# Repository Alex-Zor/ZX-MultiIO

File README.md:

Universal Expansion Board for the ZX PentaDiv Nemo
An expansion board for the ZX Spectrum clone that combines multiple I/O devices in one:

💾 Hard disk controller (Nemo IDE) 

📼 Floppy disk controller (BDI)

💡 SD card interface (z-controller)

⏰ Real-time clock (RTC)

The goal of the project is to provide a universal solution for data storage and accurate timekeeping on ZX PentaDiv NEMO computers

https://t.me/pentadiv

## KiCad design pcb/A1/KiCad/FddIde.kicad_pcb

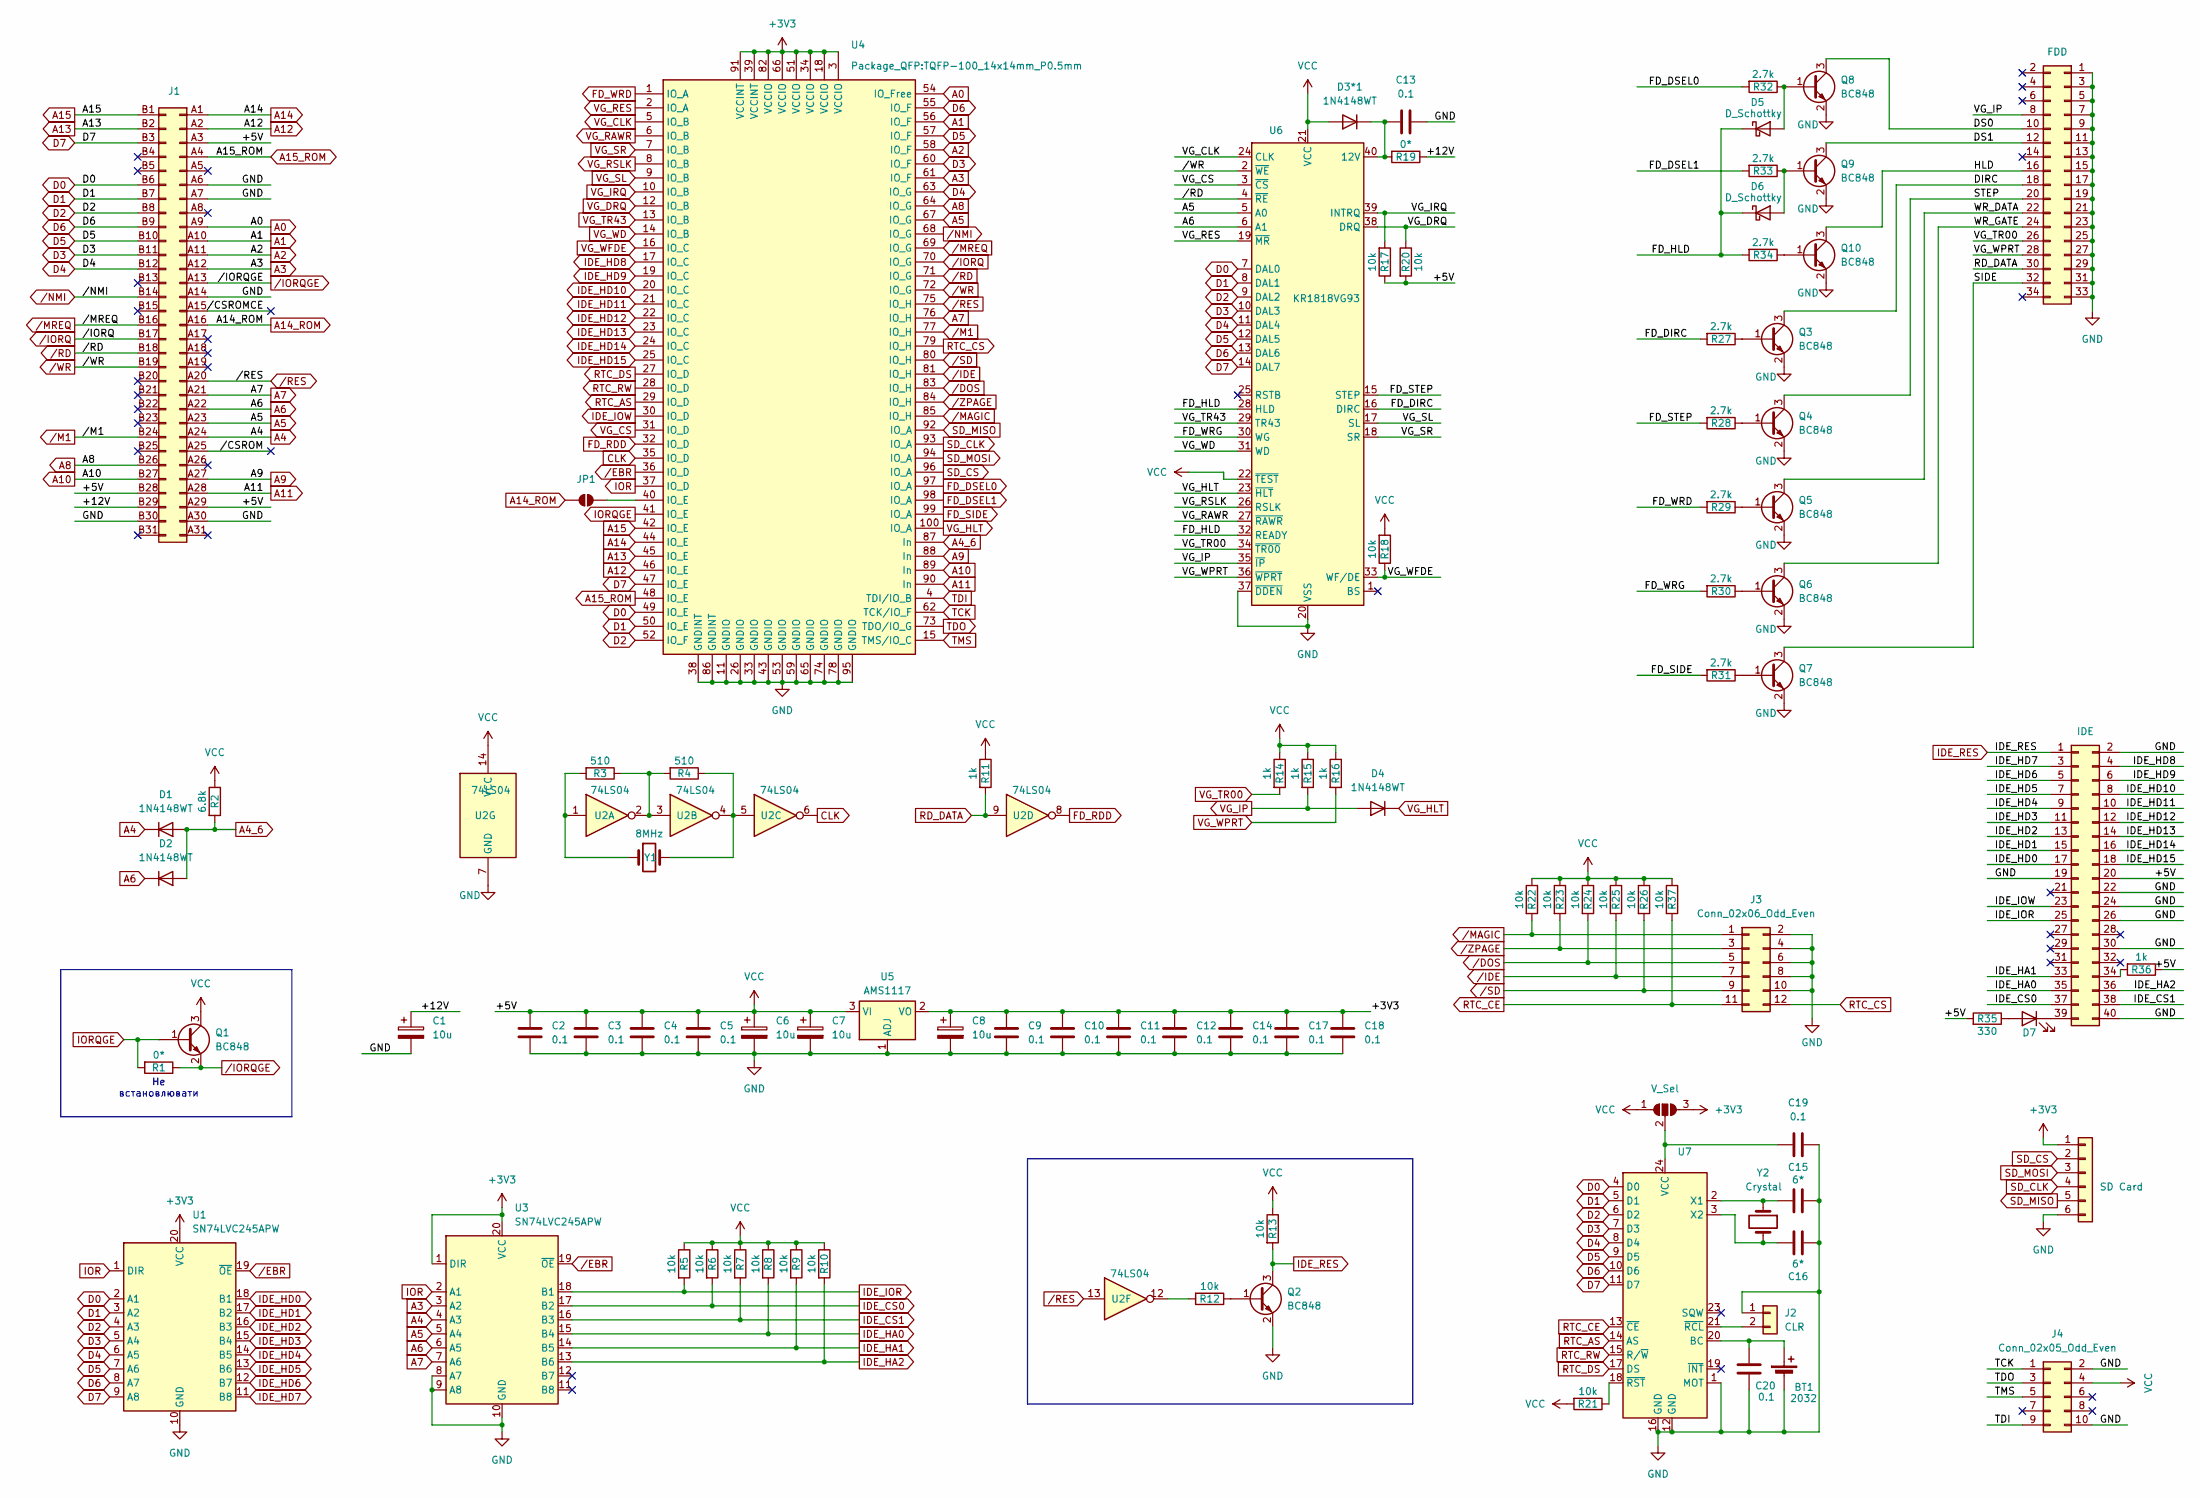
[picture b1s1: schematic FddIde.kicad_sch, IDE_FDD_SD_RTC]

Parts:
BT1: 2032; BatteryHolder_MYOUNG_BS-07-A1BJ001_CR2032
C1, C6, C7, C8: 10u; CP_Radial_D4.0mm_P2.00mm
C2, C3, C4, C5, C9, C10, C11, C12, C13, C14, C17, C18, C19, C20: 0.1; C_0805_2012Metric_Pad1.18x1.45mm_HandSolder
C15, C16: 6*; C_0805_2012Metric_Pad1.18x1.45mm_HandSolder
D1, D2, D3*1, D4: 1N4148WT; D_MiniMELF
D5, D6: D_Schottky; D_MiniMELF
D7: LED; LED_1206_3216Metric_Pad1.42x1.75mm_HandSolder
J1: Conn_02x31_Row_Letter_First; NemoBus_Edge_Connector
J2: CLR; PinHeader_1x02_P2.54mm_Vertical
J3: Conn_02x06_Odd_Even; PinHeader_2x06_P2.54mm_Vertical
J4: Conn_02x05_Odd_Even; PinHeader_2x05_P2.54mm_Vertical
J5: FDD; IDC-Header_2x17_P2.54mm_Vertical
J6: IDE; IDC-Header_2x20_P2.54mm_Vertical
J7: SD Card; PinHeader_1x06_P2.54mm_Vertical
JP1: SolderJumper_2_Open; SolderJumper-2_P1.3mm_Open_RoundedPad1.0x1.5mm
JP2: V_Sel; SolderJumper-3_P1.3mm_Open_RoundedPad1.0x1.5mm
Q1, Q2, Q3, Q4, Q5, Q6, Q7, Q8, Q9, Q10: BC848; SOT-23
R1: 0*; R_0805_2012Metric_Pad1.20x1.40mm_HandSolder
R2: 6.8k; R_0805_2012Metric_Pad1.20x1.40mm_HandSolder
R3, R4: 510; R_0805_2012Metric_Pad1.20x1.40mm_HandSolder
R5, R6, R7, R8, R9, R10, R12, R13, R17, R18, R20, R21, R22, R23, R24, R25, R26, R37: 10k; R_0805_2012Metric_Pad1.20x1.40mm_HandSolder
R11, R14, R15, R16, R36: 1k; R_0805_2012Metric_Pad1.20x1.40mm_HandSolder
R19: 0*; SolderJumper-2_P1.3mm_Open_RoundedPad1.0x1.5mm
R27, R28, R29, R30, R31, R32, R33, R34: 2.7k; R_0805_2012Metric_Pad1.20x1.40mm_HandSolder
R35: 330; R_0805_2012Metric_Pad1.20x1.40mm_HandSolder
U1, U3: SN74LVC245APW; TSSOP-20_4.4x6.5mm_P0.65mm
U2: 74LS04; DIP-14_W7.62mm
U4: TQFP-100_14x14mm_P0.5mm
U5: AMS1117; SOT-223-3_TabPin2
U6: KR1818VG93; DIP-40_W15.24mm
U7: SSOP-24_3.9x8.7mm_P0.635mm
Y1: 8MHz; Crystal_HC49-4H_Vertical
Y2: Crystal; Crystal_DS26_D2.0mm_L6.0mm_Horizontal

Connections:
+3V3: C8.1, C9.1, C10.1, C11.1, C12.1, C14.1, C17.1, C18.1, J7.1, JP2.3 (B), U1.20 (VCC), U3.1 (DIR), U3.20 (VCC), U4.3 (VCCIO), U4.18 (VCCIO), U4.34 (VCCIO), U4.39 (VCCINT), U4.51 (VCCIO), U4.66 (VCCIO), U4.82 (VCCIO), U4.91 (VCCINT), U5.2 (VO)
/+12V: C1.1, J1.B29 (Pin_b29), R19.1
/DIRC: J5.18, Q3.3 (C)
/DS0: J5.10, Q8.3 (C)
/DS1: J5.12, Q9.3 (C)
/FD_DIRC: R27.2, U6.16 (DIRC)
/FD_HLD: D5.1 (K), D6.1 (K), R34.2, U6.28 (HLD), U6.32 (READY)
/FD_STEP: R28.2, U6.15 (STEP)
/FD_WRG: R30.2, U6.30 (WG)
/HLD: J5.16, Q10.3 (C)
/SIDE: J5.32, Q7.3 (C)
/STEP: J5.20, Q4.3 (C)
/WR_DATA: J5.22, Q5.3 (C)
/WR_GATE: J5.24, Q6.3 (C)
//CSROM: J1.A25 (Pin_a25)
//CSROMCE: J1.A15 (Pin_a15)
A0: J1.A9 (Pin_a9), U4.54 (IO_Free)
A1: J1.A10 (Pin_a10), U4.56 (IO_F)
A2: J1.A11 (Pin_a11), U4.58 (IO_F)
A3: J1.A12 (Pin_a12), U3.3 (A2), U4.61 (IO_F)
A4: D1.1 (K), J1.A24 (Pin_a24), U3.4 (A3)
A4_6: D1.2 (A), D2.2 (A), R2.2, U4.87 (In)
A5: J1.A23 (Pin_a23), U3.5 (A4), U4.67 (IO_G), U6.5 (A0)
A6: D2.1 (K), J1.A22 (Pin_a22), U3.6 (A5), U6.6 (A1)
A7: J1.A21 (Pin_a21), U3.7 (A6), U4.76 (IO_H)
A8: J1.B26 (Pin_b26), U4.64 (IO_G)
A9: J1.A27 (Pin_a27), U4.88 (In)
A10: J1.B27 (Pin_b27), U4.89 (In)
A11: J1.A28 (Pin_a28), U4.90 (In)
A12: J1.A2 (Pin_a2), U4.46 (IO_E)
A13: J1.B2 (Pin_b2), U4.45 (IO_E)
A14: J1.A1 (Pin_a1), U4.44 (IO_E)
A14_ROM: J1.A16 (Pin_a16), JP1.1 (A)
A15: J1.B1 (Pin_b1), U4.42 (IO_E)
A15_ROM: J1.A4 (Pin_a4), U4.48 (IO_E)
CLK: U2.6, U4.35 (IO_D)
D0: J1.B6 (Pin_b6), U1.2 (A1), U4.49 (IO_E), U6.7 (DAL0), U7.4 (D0)
D1: J1.B7 (Pin_b7), U1.3 (A2), U4.50 (IO_E), U6.8 (DAL1), U7.5 (D1)
D2: J1.B8 (Pin_b8), U1.4 (A3), U4.52 (IO_F), U6.9 (DAL2), U7.6 (D2)
D3: J1.B11 (Pin_b11), U1.5 (A4), U4.60 (IO_F), U6.10 (DAL3), U7.7 (D3)
D4: J1.B12 (Pin_b12), U1.6 (A5), U4.63 (IO_G), U6.11 (DAL4), U7.8 (D4)
D5: J1.B10 (Pin_b10), U1.7 (A6), U4.57 (IO_F), U6.12 (DAL5), U7.9 (D5)
D6: J1.B9 (Pin_b9), U1.8 (A7), U4.55 (IO_F), U6.13 (DAL6), U7.10 (D6)
D7: J1.B3 (Pin_b3), U1.9 (A8), U4.47 (IO_E), U6.14 (DAL7), U7.11 (D7)
FD_DSEL0: R32.2, U4.97 (IO_A)
FD_DSEL1: R33.2, U4.98 (IO_A)
FD_RDD: U2.8, U4.32 (IO_D)
FD_SIDE: R31.2, U4.99 (IO_A)
FD_WRD: R29.2, U4.1 (IO_A)
GND: BT1.2 (-), C1.2, C2.2, C3.2, C4.2, C5.2, C6.2, C7.2, C8.2, C9.2, C10.2, C11.2, C12.2, C13.2, C14.2, C15.2, C16.2, C17.2, C18.2, C19.2, C20.2, J1.A6 (Pin_a6), J1.A7 (Pin_a7), J1.A14 (Pin_a14), J1.A30 (Pin_a30), J1.B30 (Pin_b30), J2.1, J3.2, J3.4, J3.6, J3.8, J3.10, J4.2, J4.10, J5.1, J5.3, J5.5, J5.7, J5.9, J5.11, J5.13, J5.15, J5.17, J5.19, J5.21, J5.23, J5.25, J5.27, J5.29, J5.31, J5.33, J6.2, J6.19, J6.22, J6.24, J6.26, J6.30, J6.40, J7.6, Q2.2 (E), Q3.2 (E), Q4.2 (E), Q5.2 (E), Q6.2 (E), Q7.2 (E), Q8.2 (E), Q9.2 (E), Q10.2 (E), U1.10 (GND), U2.7 (GND), U3.8 (A7), U3.9 (A8), U3.10 (GND), U4.11 (GNDIO), U4.26 (GNDIO), U4.33 (GNDIO), U4.38 (GNDINT), U4.43 (GNDIO), U4.53 (GNDIO), U4.59 (GNDIO), U4.65 (GNDIO), U4.74 (GNDIO), U4.78 (GNDIO), U4.86 (GNDINT), U4.95 (GNDIO), U5.1 (ADJ), U6.20 (VSS), U6.37 (~DDEN), U7.1 (MOT), U7.12 (GND), U7.16 (GND)
IDE_CS0: J6.37, R6.2, U3.17 (B2)
IDE_CS1: J6.38, R7.2, U3.16 (B3)
IDE_HA0: J6.35, R8.2, U3.15 (B4)
IDE_HA1: J6.33, R9.2, U3.14 (B5)
IDE_HA2: J6.36, R10.2, U3.13 (B6)
IDE_HD0: J6.17, U1.18 (B1)
IDE_HD1: J6.15, U1.17 (B2)
IDE_HD2: J6.13, U1.16 (B3)
IDE_HD3: J6.11, U1.15 (B4)
IDE_HD4: J6.9, U1.14 (B5)
IDE_HD5: J6.7, U1.13 (B6)
IDE_HD6: J6.5, U1.12 (B7)
IDE_HD7: J6.3, U1.11 (B8)
IDE_HD8: J6.4, U4.17 (IO_C)
IDE_HD9: J6.6, U4.19 (IO_C)
IDE_HD10: J6.8, U4.20 (IO_C)
IDE_HD11: J6.10, U4.21 (IO_C)
IDE_HD12: J6.12, U4.22 (IO_C)
IDE_HD13: J6.14, U4.23 (IO_C)
IDE_HD14: J6.16, U4.24 (IO_C)
IDE_HD15: J6.18, U4.25 (IO_C)
IDE_IOR: J6.25, R5.2, U3.18 (B1)
IDE_IOW: J6.23, U4.30 (IO_D)
IDE_RES: J6.1, Q2.3 (C), R13.2
IOR: U1.1 (DIR), U3.2 (A1), U4.37 (IO_D)
IORQGE: Q1.1 (B), R1.2, U4.41 (IO_E)
unnamed: BT1.1 (+), C20.1, U7.20 (BC)
unnamed: C13.1, D3*1.1 (K), R19.2, U6.40 (12V)
unnamed: D5.2 (A), Q8.1 (B), R32.1
unnamed: D6.2 (A), Q9.1 (B), R33.1
unnamed: D7.2 (A), R35.1
unnamed: D7.1 (K), J6.39
unnamed: J2.2, U7.21 (~RCL)
unnamed: J6.34, R36.2
unnamed: JP1.2 (B), U4.40 (IO_E)
unnamed: C19.1, JP2.2 (C), U7.24 (VCC)
unnamed: Q2.1 (B), R12.1
unnamed: Q3.1 (B), R27.1
unnamed: Q4.1 (B), R28.1
unnamed: Q5.1 (B), R29.1
unnamed: Q6.1 (B), R30.1
unnamed: Q7.1 (B), R31.1
unnamed: Q10.1 (B), R34.1
unnamed: R3.1, R4.2, U2.2, U2.3
unnamed: R3.2, U2.1, Y1.1
unnamed: R4.1, U2.4, U2.5, Y1.2
unnamed: R12.2, U2.12
unnamed: C15.1, U7.2 (X1), Y2.1
unnamed: C16.1, U7.3 (X2), Y2.2
unnamed: R21.1, U7.18 (~RST)
RD_DATA: J5.30, R11.2, U2.9
RTC_AS: U4.29 (IO_D), U7.14 (AS)
RTC_CE: J3.11, R37.2, U7.13 (~CE)
RTC_CS: J3.12, U4.79 (IO_H)
RTC_DS: U4.27 (IO_D), U7.17 (DS)
RTC_RW: U4.28 (IO_D), U7.15 (R/~W)
SD_CLK: J7.4, U4.93 (IO_A)
SD_CS: J7.2, U4.96 (IO_A)
SD_MISO: J7.5, U4.92 (IO_A)
SD_MOSI: J7.3, U4.94 (IO_A)
TCK: J4.1, U4.62 (TCK/IO_F)
TDI: J4.9, U4.4 (TDI/IO_B)
TDO: J4.3, U4.73 (TDO/IO_G)
TMS: J4.5, U4.15 (TMS/IO_C)
VCC: C2.1, C3.1, C4.1, C5.1, C6.1, C7.1, D3*1.2 (A), J1.A3 (Pin_a3), J1.A29 (Pin_a29), J1.B28 (Pin_b28), J4.4, J6.20, JP2.1 (A), Q1.3 (C), R2.1, R5.1, R6.1, R7.1, R8.1, R9.1, R10.1, R11.1, R13.1, R14.1, R15.1, R16.1, R17.1, R18.2, R20.2, R21.2, R22.1, R23.1, R24.1, R25.1, R26.1, R35.2, R36.1, R37.1, U2.14 (VCC), U5.3 (VI), U6.21 (VCC), U6.22 (~TEST)
VG_CLK: U4.5 (IO_B), U6.24 (CLK)
VG_CS: U4.31 (IO_D), U6.3 (~CS)
VG_DRQ: R20.1, U4.12 (IO_B), U6.38 (DRQ)
VG_HLT: D4.1 (K), U4.100 (IO_A), U6.23 (~HLT)
VG_IP: D4.2 (A), J5.8, R15.2, U6.35 (~IP)
VG_IRQ: R17.2, U4.10 (IO_B), U6.39 (INTRQ)
VG_RAWR: U4.6 (IO_B), U6.27 (~RAWR)
VG_RES: U4.2 (IO_A), U6.19 (~MR)
VG_RSLK: U4.8 (IO_B), U6.26 (RSLK)
VG_SL: U4.9 (IO_B), U6.17 (SL)
VG_SR: U4.7 (IO_B), U6.18 (SR)
VG_TR00: J5.26, R14.2, U6.34 (~TR00)
VG_TR43: U4.13 (IO_B), U6.29 (TR43)
VG_WD: U4.14 (IO_B), U6.31 (WD)
VG_WFDE: R18.1, U4.16 (IO_C), U6.33 (WF/DE)
VG_WPRT: J5.28, R16.2, U6.36 (~WPRT)
/DOS: J3.5, R24.2, U4.83 (IO_H)
/EBR: U1.19 (~OE), U3.19 (~OE), U4.36 (IO_D)
/IDE: J3.7, R25.2, U4.81 (IO_H)
/IORQ: J1.B17 (Pin_b17), U4.70 (IO_G)
/IORQGE: J1.A13 (Pin_a13), Q1.2 (E), R1.1
/M1: J1.B24 (Pin_b24), U4.77 (IO_H)
/MAGIC: J3.1, R22.2, U4.85 (IO_H)
/MREQ: J1.B16 (Pin_b16), U4.69 (IO_G)
/NMI: J1.B14 (Pin_b14), U4.68 (IO_G)
/RD: J1.B18 (Pin_b18), U4.71 (IO_G), U6.4 (~RE)
/RES: J1.A20 (Pin_a20), U2.13, U4.75 (IO_H)
/SD: J3.9, R26.2, U4.80 (IO_H)
/WR: J1.B19 (Pin_b19), U4.72 (IO_G), U6.2 (~WE)
/ZPAGE: J3.3, R23.2, U4.84 (IO_H)

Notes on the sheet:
Не встановлювати

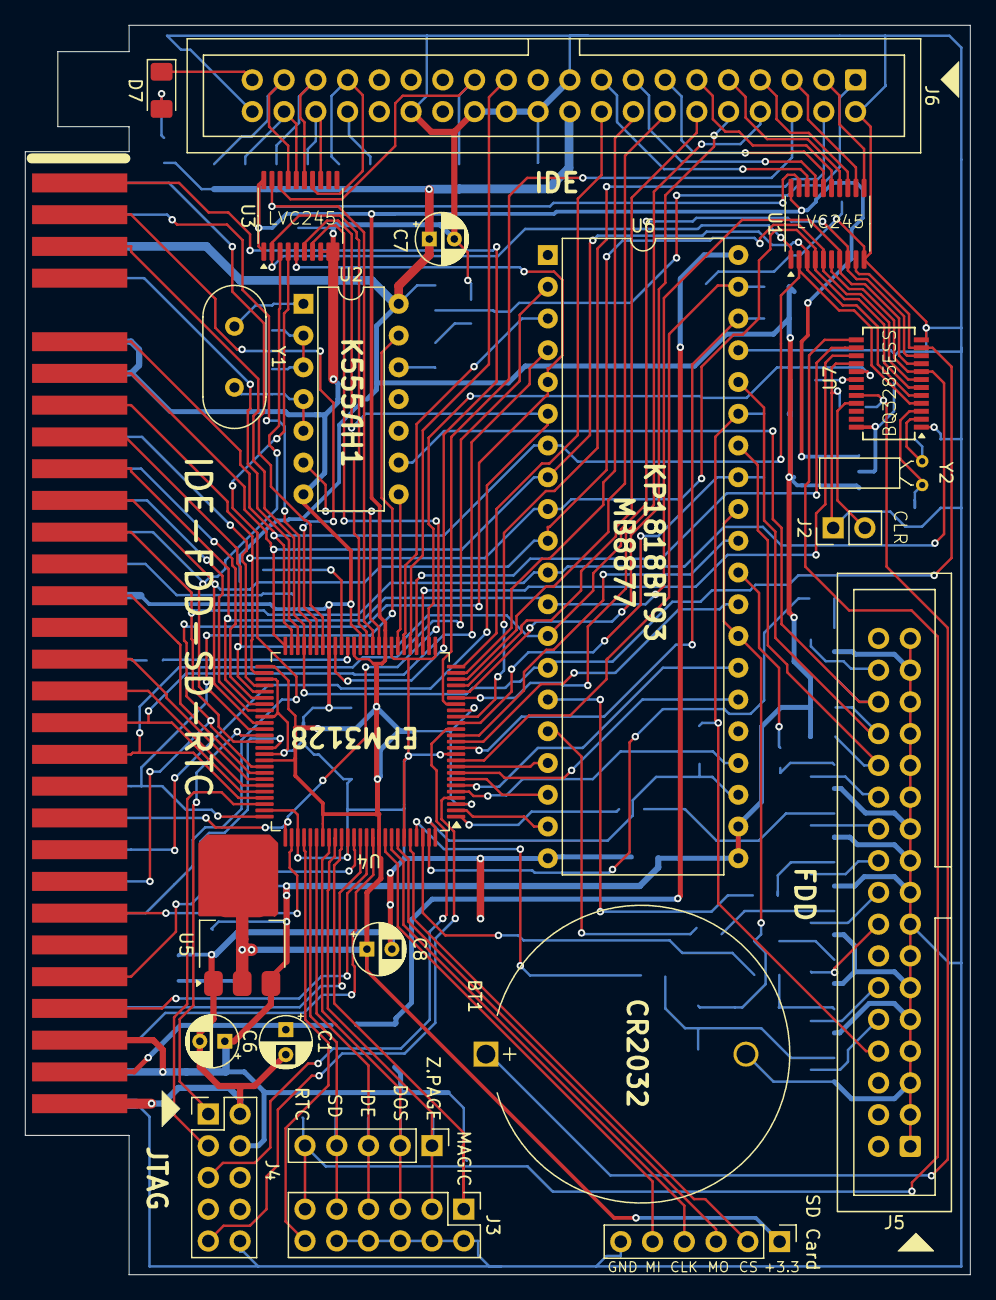
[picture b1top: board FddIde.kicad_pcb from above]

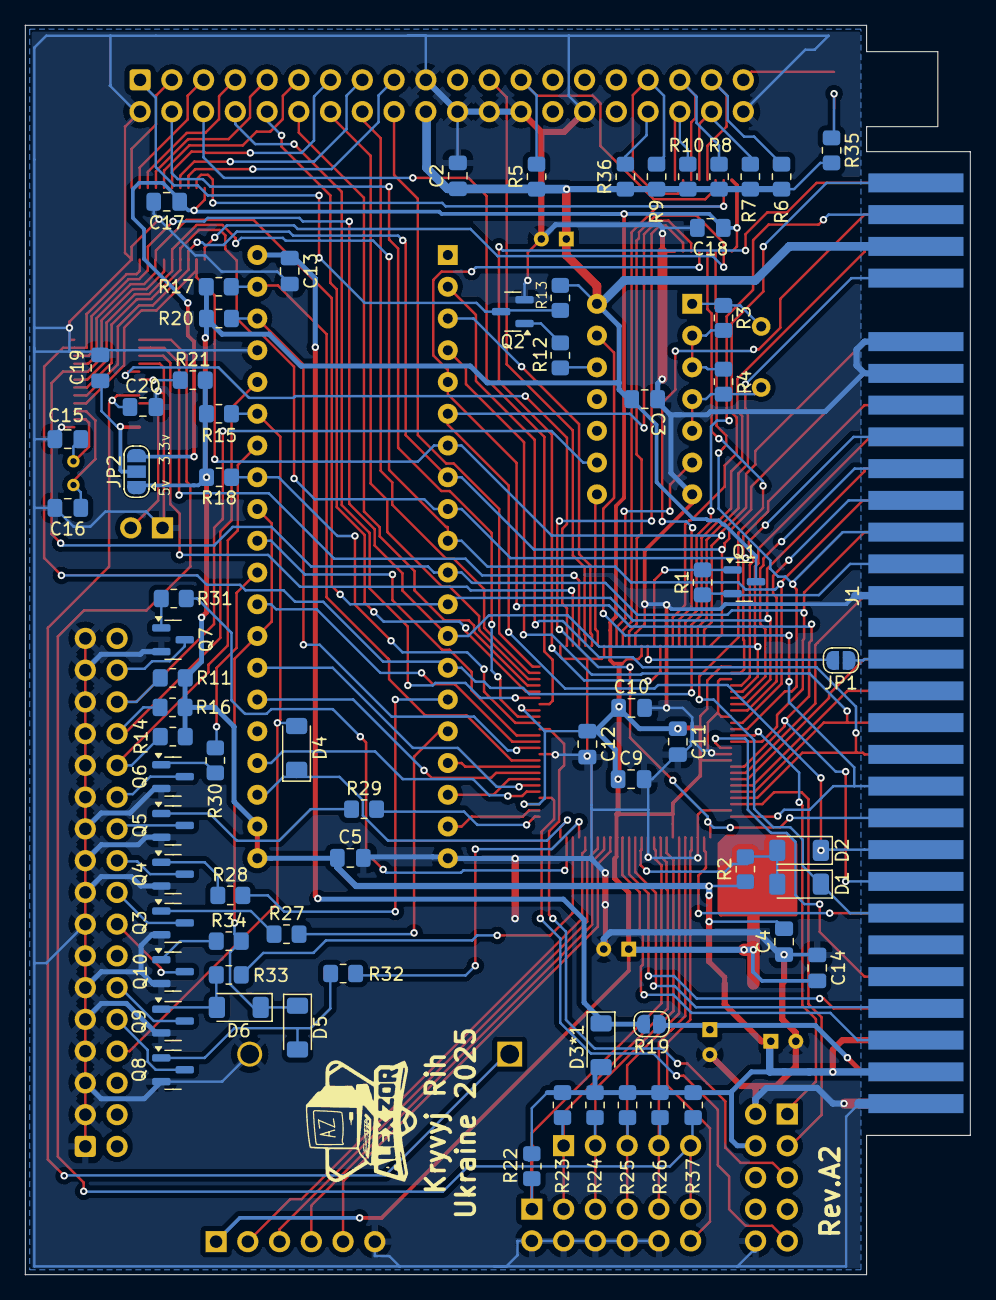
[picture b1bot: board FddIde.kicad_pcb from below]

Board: 2 copper layers, 75.6 x 99.9 mm, 93 parts (72 on the bottom side), 143 nets.

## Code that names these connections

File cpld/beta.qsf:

# -------------------------------------------------------------------------- #
#
# Copyright (C) 1991-2013 Altera Corporation
# Your use of Altera Corporation's design tools, logic functions 
# and other software and tools, and its AMPP partner logic 
# functions, and any output files from any of the foregoing 
# (including device programming or simulation files), and any 
# associated documentation or information are expressly subject 
# to the terms and conditions of the Altera Program License 
# Subscription Agreement, Altera MegaCore Function License 
# Agreement, or other applicable license agreement, including, 
# without limitation, that your use is for the sole purpose of 
# programming logic devices manufactured by Altera and sold by 
# Altera or its authorized distributors.  Please refer to the 
# applicable agreement for further details.
#
# -------------------------------------------------------------------------- #
#
# Quartus II 64-Bit
# Version 13.0.1 Build 232 06/12/2013 Service Pack 1 SJ Web Edition
# Date created = 22:50:21  March 08, 2025
#
# -------------------------------------------------------------------------- #
#
# Notes:
#
# 1) The default values for assignments are stored in the file:
#		beta_assignment_defaults.qdf
#    If this file doesn't exist, see file:
#		assignment_defaults.qdf
#
# 2) Altera recommends that you do not modify this file. This
#    file is updated automatically by the Quartus II software
#    and any changes you make may be lost or overwritten.
#
# -------------------------------------------------------------------------- #


set_global_assignment -name FAMILY MAX3000A
set_global_assignment -name DEVICE "EPM3128ATC100-10"
set_global_assignment -name TOP_LEVEL_ENTITY beta
set_global_assignment -name ORIGINAL_QUARTUS_VERSION "13.0 SP1"
set_global_assignment -name PROJECT_CREATION_TIME_DATE "22:50:21  MARCH 08, 2025"
set_global_assignment -name LAST_QUARTUS_VERSION "13.0 SP1"
set_global_assignment -name PROJECT_OUTPUT_DIRECTORY output_files
set_global_assignment -name ERROR_CHECK_FREQUENCY_DIVISOR "-1"
set_global_assignment -name VHDL_FILE beta.vhd
set_global_assignment -name OPTIMIZE_HOLD_TIMING OFF
set_global_assignment -name OPTIMIZE_MULTI_CORNER_TIMING OFF
set_global_assignment -name FITTER_EFFORT "STANDARD FIT"
set_global_assignment -name MAX7000_DEVICE_IO_STANDARD "3.3-V LVTTL"
set_location_assignment PIN_30 -to IDE_IOW
set_location_assignment PIN_2 -to VG_RES
set_location_assignment PIN_100 -to VG_HLT
set_location_assignment PIN_31 -to VG_CS
set_location_assignment PIN_5 -to VG_CLK
set_location_assignment PIN_6 -to VG_RAWR
set_location_assignment PIN_8 -to VG_RSLK
set_location_assignment PIN_7 -to VG_SR
set_location_assignment PIN_9 -to VG_SL
set_location_assignment PIN_13 -to VG_TR43
set_location_assignment PIN_14 -to VG_WD
set_location_assignment PIN_97 -to FD_DSEL0
set_location_assignment PIN_98 -to FD_DSEL1
set_location_assignment PIN_99 -to FD_SIDE
set_location_assignment PIN_1 -to FD_WRD
set_location_assignment PIN_25 -to IDE_HD[15]
set_location_assignment PIN_23 -to IDE_HD[13]
set_location_assignment PIN_22 -to IDE_HD[12]
set_location_assignment PIN_77 -to M1
set_location_assignment PIN_75 -to RESET
set_location_assignment PIN_72 -to WR
set_location_assignment PIN_71 -to RD
set_location_assignment PIN_70 -to IORQ
set_location_assignment PIN_69 -to MREQ
set_location_assignment PIN_68 -to NMI
set_location_assignment PIN_63 -to D[4]
set_location_assignment PIN_60 -to D[3]
set_location_assignment PIN_57 -to D[5]
set_location_assignment PIN_55 -to D[6]
set_location_assignment PIN_52 -to D[2]
set_location_assignment PIN_50 -to D[1]
set_location_assignment PIN_49 -to D[0]
set_location_assignment PIN_48 -to A15ROM
set_location_assignment PIN_47 -to D[7]
set_location_assignment PIN_41 -to IORQGE
set_location_assignment PIN_35 -to CLKIN
set_location_assignment PIN_10 -to VG_IRQ
set_location_assignment PIN_12 -to VG_DRQ
set_location_assignment PIN_32 -to FD_RDD
set_location_assignment PIN_21 -to IDE_HD[11]
set_location_assignment PIN_17 -to IDE_HD[8]
set_location_assignment PIN_19 -to IDE_HD[9]
set_location_assignment PIN_20 -to IDE_HD[10]
set_location_assignment PIN_37 -to BF_IOR
set_location_assignment PIN_36 -to BF_EBL
set_location_assignment PIN_81 -to BT_IDE
set_location_assignment PIN_85 -to BT_MAGIC
set_location_assignment PIN_84 -to BT_ZPAGE
set_location_assignment PIN_83 -to BT_DOS
set_global_assignment -name MAX7000_OPTIMIZATION_TECHNIQUE AREA
set_global_assignment -name SYNTH_TIMING_DRIVEN_SYNTHESIS OFF
set_location_assignment PIN_29 -to RTC_AS
set_location_assignment PIN_79 -to RTC_CS
set_location_assignment PIN_27 -to RTC_DS
set_location_assignment PIN_28 -to RTC_RW
set_location_assignment PIN_80 -to BT_SD
set_location_assignment PIN_93 -to SD_CLK
set_location_assignment PIN_96 -to SD_CS
set_location_assignment PIN_92 -to SD_MISO
set_location_assignment PIN_94 -to SD_MOSI
set_location_assignment PIN_44 -to Ah[14]
set_location_assignment PIN_40 -to A14ROM
set_location_assignment PIN_42 -to Ah[15]
set_location_assignment PIN_45 -to Ah[13]
set_location_assignment PIN_46 -to Ah[12]
set_location_assignment PIN_54 -to Al[0]
set_location_assignment PIN_56 -to Al[1]
set_location_assignment PIN_58 -to Al[2]
set_location_assignment PIN_61 -to Al[3]
set_location_assignment PIN_64 -to Ah[8]
set_location_assignment PIN_67 -to Al[5]
set_location_assignment PIN_76 -to Ah[7]
set_location_assignment PIN_87 -to Al[4]
set_location_assignment PIN_88 -to Ah[9]
set_location_assignment PIN_89 -to Ah[10]
set_location_assignment PIN_90 -to Ah[11]
set_location_assignment PIN_16 -to VG_WFDE
set_location_assignment PIN_24 -to IDE_HD[14]

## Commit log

2025-06-28 Create note
